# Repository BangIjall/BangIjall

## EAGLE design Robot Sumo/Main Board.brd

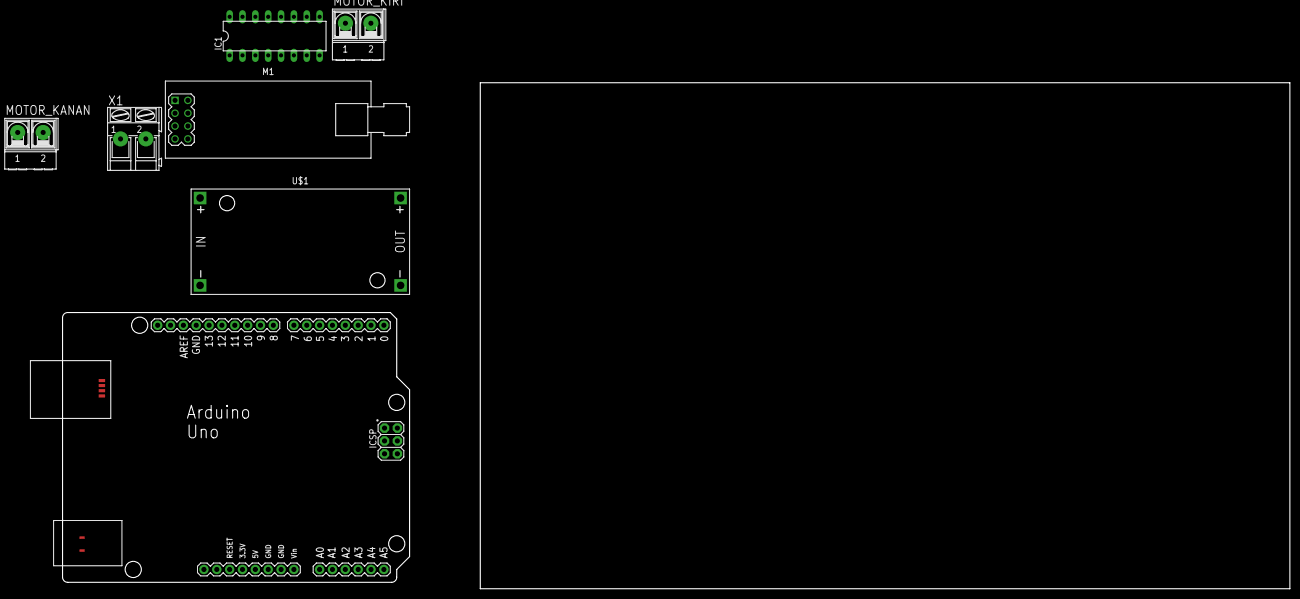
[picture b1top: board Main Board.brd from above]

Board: 2 copper layers, 242.6 x 100.0 mm, 7 parts (0 on the bottom side), 5 nets, no tracks yet.

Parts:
IC1: L293D; DIL16
M1: WIRELESS-NRF24L01-PA-EXT
MOTOR_KANAN: AK500/2-H
MOTOR_KIRI: AK500/2-H
PCB1: ARDUINO_UNO
U$1: DC-DC-STEP-DOWN-LM2596
X1: AK300/2

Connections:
5V: M1.2, PCB1.5V
6V: PCB1.<USB>+V, PCB1.VIN, U$1.OUT+
GND: M1.1, PCB1.GND.., U$1.OUT-
unnamed: U$1.IN+, X1.1
unnamed: U$1.IN-, X1.2

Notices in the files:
parts and their libraries:
diy-modules: Released under the Creative Commons Attribution 4.0 International License: http://creativecommons.org/licenses/by/4.0
